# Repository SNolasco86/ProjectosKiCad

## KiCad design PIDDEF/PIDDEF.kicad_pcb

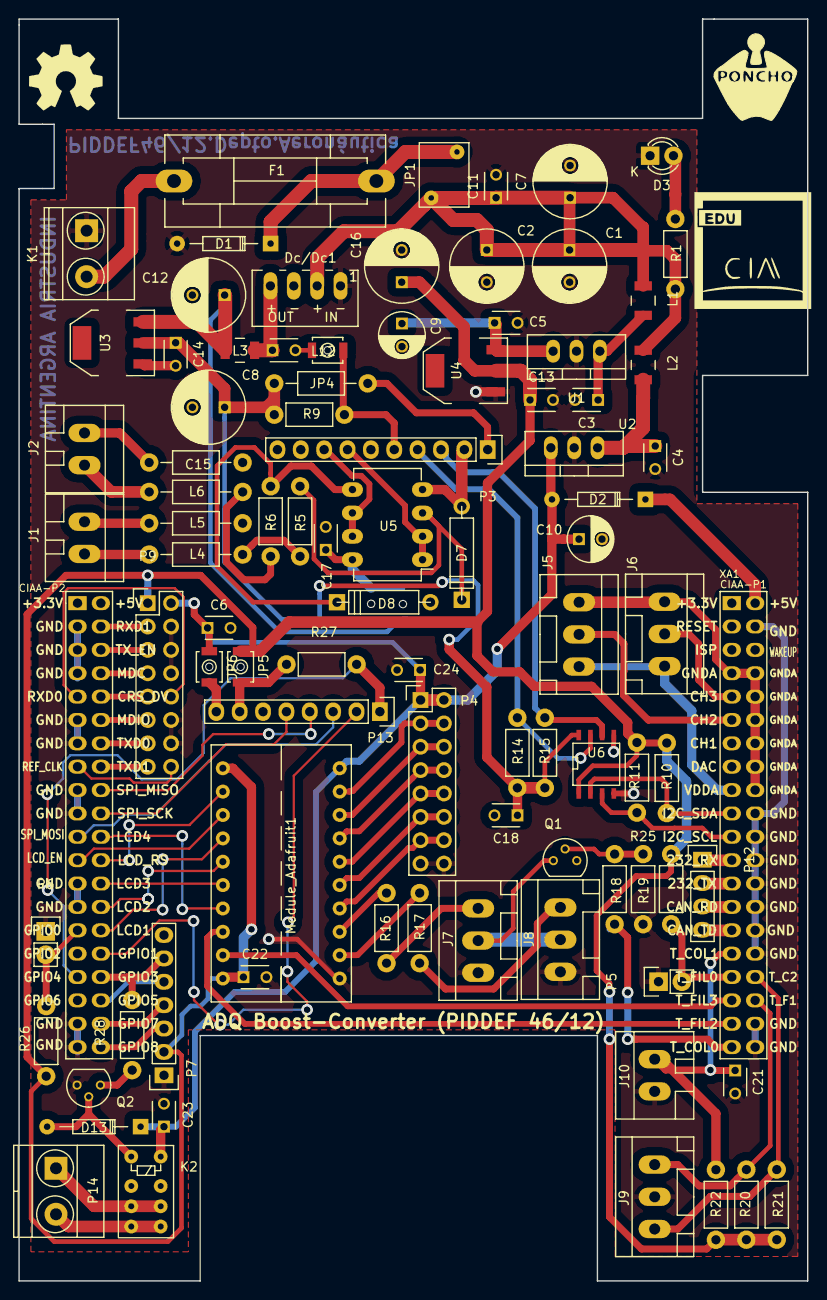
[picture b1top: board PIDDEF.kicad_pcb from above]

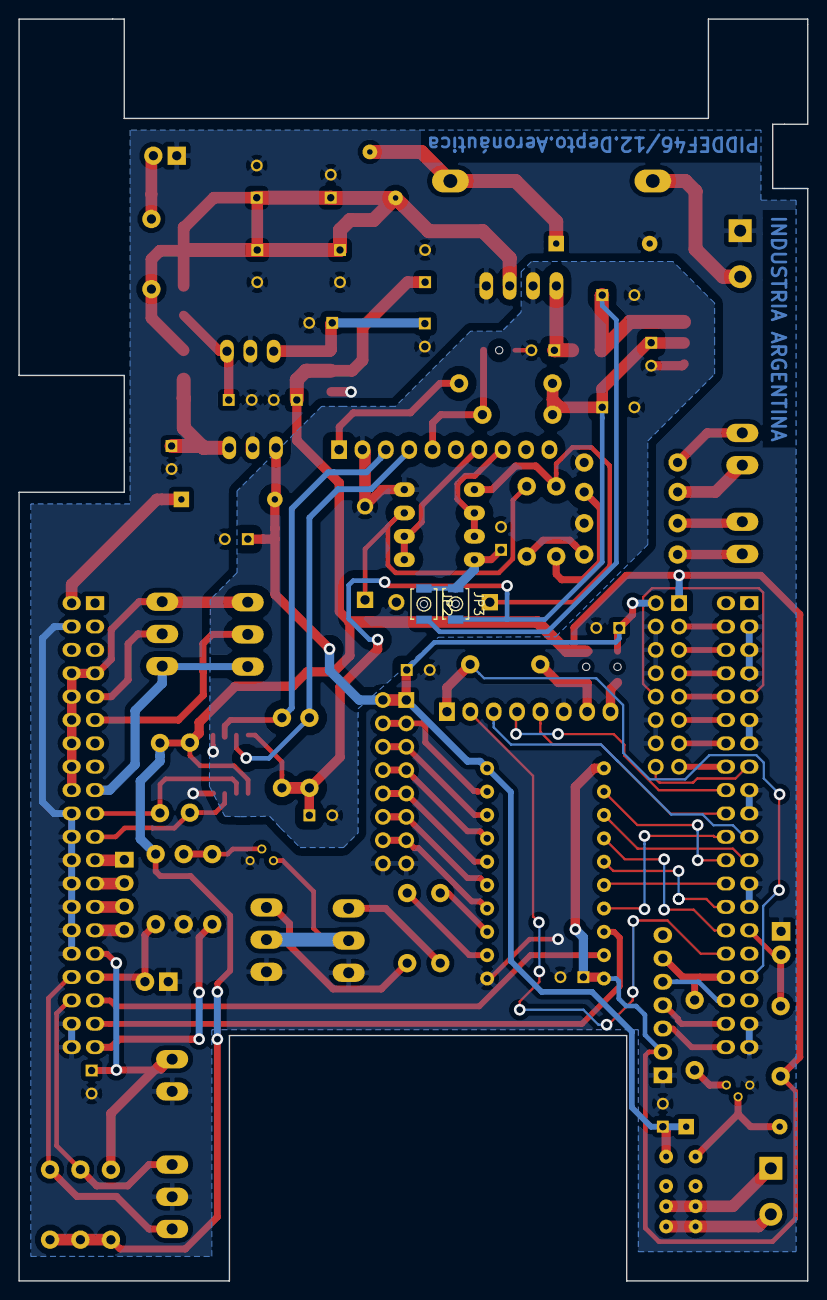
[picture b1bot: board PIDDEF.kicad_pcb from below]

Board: 2 copper layers, 85.7 x 137.2 mm, 94 parts (2 on the bottom side), 90 nets.

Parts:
C1, C2, C7, C12, C15, C16: CP1; C_Radial_D8_L11.5_P3.5
C3, C4, C5, C6, C8, C11, C13, C14, C17, C18, C21, C22, C23, C24: C; C_Disc_D3_P2.5
C9, C10: CP1; C_Radial_D5_L6_P2.5
D1, D2: D; Diode_DO-35_SOD27_Horizontal_RM10
D3: LED; LED-3MM
D7, D8: ZENER; D4
D13: D_Small; Diode_DO-35_SOD27_Horizontal_RM10
Dc/Dc1: TME_1205S; DCDC-Conv_TRACO_TME05xx_TME12xx
F1: FUSE; Fuseholder5x20_horiz_SemiClosed_Casing10x25mm
G101: Logo_OSHWA
J1, J2, J10: HEADER_2; WAGO_734_2pin_Straight_RuggedPads
J5, J6, J7, J8, J9: HEADER_3; WAGO_734_3pin_Straight_RuggedPads
JP1: JUMPER; RV_Disc_D7_W5.4_P5
JP2, JP3, JP4, JP5, JP6: Jumper_NO_Small; SW_SPST_B3U-1000P-B
K1: CONN_2; TerminalBlock_Pheonix_MKDS1.5-2pol
K2: RELAY_2RT; Relay_DPDT_IM0(3,6,7)NS
L1, L2, L3: L_Small; Neosid_Inductor_SM-NE30_SMD1210
L4, L5, L6, L7, L12: INDUCTOR; Resistor_Horizontal_RM10mm
Module_Adafruit1: Module_LevelShifter; Adafruit-LevelShifter-TXB0108
P3: CONN_01X10; Socket_Strip_Straight_1x10
P4, P9: CONN_02X08; Pin_Header_Straight_2x08
P5, P6: CONN_01X02; Pin_Header_Straight_1x02
P7: CONN_01X07; Socket_Strip_Straight_1x07
P12: CONN_01X04; Socket_Strip_Straight_1x04
P13: CONN_01X08; Socket_Strip_Straight_1x08
P14: CONN_01X02; TerminalBlock_Pheonix_MKDS1.5-2pol
Power ADQ: LOGO; Logo_Poncho
Q1: Q_NMOS_DGS; TO-92_Molded_Narrow
Q2: Q_NPN_BCE; TO-92_Molded_Narrow
R1, R5, R6, R9, R10, R11, R14, R15, R16, R17, R18, R19, R20, R21, R22, R25, R26, R27, R28: R; Resistor_Horizontal_RM7mm
U1, U2: 7805correg; TO-220_Neutral123_Vertical
U3, U4: NCP1117ST33T3G; SOT-223
U5: LM358; DIP-8_W7.62mm_LongPads
U6: AduM1251; SOIC-8-N
XA1: Conn_Poncho2P_2x_20x2; Conn_Poncho_SinBorde

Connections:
+3.3VADC: J5.3, J6.3, XA1.17
+5VD: D2.1, XA1.2
/Circuito Principal/ADC2: J5.2, XA1.11
/Circuito Principal/ADC3: J6.2, XA1.9
/Circuito Principal/ADC/+3.3V: C13.1, C16.1, C22.1, JP5.1, Module_Adafruit1.1, Module_Adafruit1.10, P7.2, P9.1, R10.2, R11.2, R20.2, R21.2, R22.1, R25.1, R26.1, U4.2, U6.1
/Circuito Principal/ADC/+3.3V(aislado): C14.1, C15.1, C18.1, JP3.2, L12.1, R9.1, R14.2, R15.2, U3.2, U6.8
/Circuito Principal/ADC/+5V(aislado): C12.1, JP2.2, L3.2, U3.3
/Circuito Principal/ADC/A0: P3.7, U5.1, U5.2
/Circuito Principal/ADC/A1: P3.8, U5.6, U5.7
/Circuito Principal/ADC/addr: JP4.1, P3.5, R9.2
/Circuito Principal/ADC/scl: P3.3, R15.1, U6.6
/Circuito Principal/ADC/sda: P3.4, R14.1, U6.7
/Circuito Principal/COL0: R18.2, XA1.39
/Circuito Principal/COL1: C21.1, J10.2, R22.2, XA1.31
/Circuito Principal/COL2: J9.1, R21.1, XA1.34
/Circuito Principal/COMUNICACION/+5V: C6.1, C10.1, C23.1, C24.1, D2.2, D13.1, JP6.1, K2.8, Module_Adafruit1.20, P4.1, P4.2, P9.2, U2.3
/Circuito Principal/CRS: P9.9, XA1.50
/Circuito Principal/F0: P5.2, R25.2, XA1.33
/Circuito Principal/F1: J9.3, R20.1, XA1.36
/Circuito Principal/F2: Module_Adafruit1.8, XA1.37
/Circuito Principal/F3: Module_Adafruit1.9, XA1.35
/Circuito Principal/Fuente/+5aV: C5.1, C9.1, U1.3, U4.3
/Circuito Principal/Fuente/+12V: C1.1, C2.1, C7.1, C11.1, Dc/Dc1.2, JP1.2, L1.1, L2.1, R1.1
/Circuito Principal/GPIO0: P6.2, R26.2, XA1.69
/Circuito Principal/GPIO1: P13.2, XA1.72
/Circuito Principal/GPIO3: P7.6, R28.2, XA1.74
/Circuito Principal/GPIO4: P13.1, R27.2, XA1.73
/Circuito Principal/GPIO5: P7.5, XA1.76
/Circuito Principal/GPIO7: P7.4, XA1.78
/Circuito Principal/GPIO8: P7.3, XA1.80
/Circuito Principal/LCD1: Module_Adafruit1.4, XA1.70
/Circuito Principal/LCD2: Module_Adafruit1.5, XA1.68
/Circuito Principal/LCD3: Module_Adafruit1.6, XA1.66
/Circuito Principal/LCD4: Module_Adafruit1.7, XA1.62
/Circuito Principal/LCD y DRIVER/LCD1-1: Module_Adafruit1.17, P4.7, P4.8
/Circuito Principal/LCD y DRIVER/LCD2-1: Module_Adafruit1.16, P4.9, P4.10
/Circuito Principal/LCD y DRIVER/LCD3-1: Module_Adafruit1.15, P4.11, P4.12
/Circuito Principal/LCD y DRIVER/LCD4-1: Module_Adafruit1.14, P4.13, P4.14
/Circuito Principal/LCD y DRIVER/LCD-EN-1: Module_Adafruit1.18, P4.5, P4.6
/Circuito Principal/LCD y DRIVER/LCD-RS-1: Module_Adafruit1.19, P4.3, P4.4
/Circuito Principal/LCD y DRIVER/PWM1out-1: Module_Adafruit1.13, R16.1
/Circuito Principal/LCD y DRIVER/PWM2out-1: Module_Adafruit1.12, R17.1
/Circuito Principal/LCD_EN: Module_Adafruit1.3, XA1.63
/Circuito Principal/MDC: P9.7, XA1.48
/Circuito Principal/MDIO: P9.11, XA1.52
/Circuito Principal/MISO: P13.4, XA1.58
/Circuito Principal/MOSI: P13.3, XA1.61
/Circuito Principal/RCLK: P9.16, XA1.55
/Circuito Principal/RD: P12.3, XA1.27
/Circuito Principal/RS: Module_Adafruit1.2, XA1.64
/Circuito Principal/RXD: P12.1, XA1.23
/Circuito Principal/RXD0: P9.10, XA1.49
/Circuito Principal/RXD1: P9.3, XA1.44
/Circuito Principal/SCL: R10.1, U6.3, XA1.21
/Circuito Principal/SD/3.3v: JP5.2, P13.7, R27.1
/Circuito Principal/SD/5v: JP6.2, P13.8
/Circuito Principal/SDA: R11.1, U6.2, XA1.19
/Circuito Principal/TD: P12.4, XA1.29
/Circuito Principal/TXD: P12.2, XA1.25
/Circuito Principal/TXD0: P9.13, XA1.54
/Circuito Principal/TXD1: P9.15, XA1.56
/Circuito Principal/TXEN: P9.5, XA1.46
/Circuito Principal/spiCCK: P13.5, XA1.60
GND: C1.2, C2.2, C3.2, C4.2, C5.2, C6.2, C7.2, C9.2, C10.2, C11.2, C13.2, C16.2, C21.2, C22.2, C23.2, C24.2, D1.2, D3.1, Dc/Dc1.1, J7.1, J8.1, J9.2, J10.1, K1.1, Module_Adafruit1.11, P4.15, P4.16, P5.1, P6.1, P7.1, P9.4, P9.6, P9.8, P9.12, P9.14, P13.6, Q1.3, Q2.3, R19.2, U1.2, U2.2, U4.1, U6.4, XA1.4, XA1.20, XA1.22, XA1.24, XA1.26, XA1.28, XA1.30, XA1.32, XA1.38, XA1.40, XA1.43, XA1.45, XA1.47, XA1.51, XA1.53, XA1.57, XA1.59, XA1.65, XA1.67, XA1.77, XA1.79
GNDA: J5.1, J6.1, XA1.7, XA1.8, XA1.10, XA1.12, XA1.14, XA1.16, XA1.18
GNDPWR: C8.2, C12.2, C14.2, C15.2, C17.2, C18.2, D7.2, D8.2, Dc/Dc1.3, JP4.2, L5.2, L7.2, P3.2, U3.1, U5.4, U6.5
unnamed: C3.1, L1.2, U1.1
unnamed: C4.1, L2.2, U2.1
unnamed: C8.1, Dc/Dc1.4, L3.1
unnamed: C17.1, JP2.1, JP3.1, U5.8
unnamed: D1.1, F1.2, JP1.1
unnamed: D3.2, R1.2
unnamed: D7.1, R5.1, U5.3
unnamed: D8.1, R6.1, U5.5
unnamed: D13.2, K2.1, Q2.2
unnamed: F1.1, K1.2
unnamed: J1.1, L5.1
unnamed: J1.2, L4.1
unnamed: J2.1, L7.1
unnamed: J2.2, L6.1
unnamed: J7.2, J8.2, Q1.1
unnamed: J7.3, R16.2
unnamed: J8.3, R17.2
unnamed: K2.3, K2.6, P14.1
unnamed: K2.4, K2.5, P14.2
unnamed: L4.2, R5.2
unnamed: L6.2, R6.2
unnamed: L12.2, P3.1
unnamed: Q1.2, R18.1, R19.1
unnamed: Q2.1, R28.1

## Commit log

2017-03-30 Proyecto PIDDEF46/12
2017-03-30 agregado .jpg y .pdfs
